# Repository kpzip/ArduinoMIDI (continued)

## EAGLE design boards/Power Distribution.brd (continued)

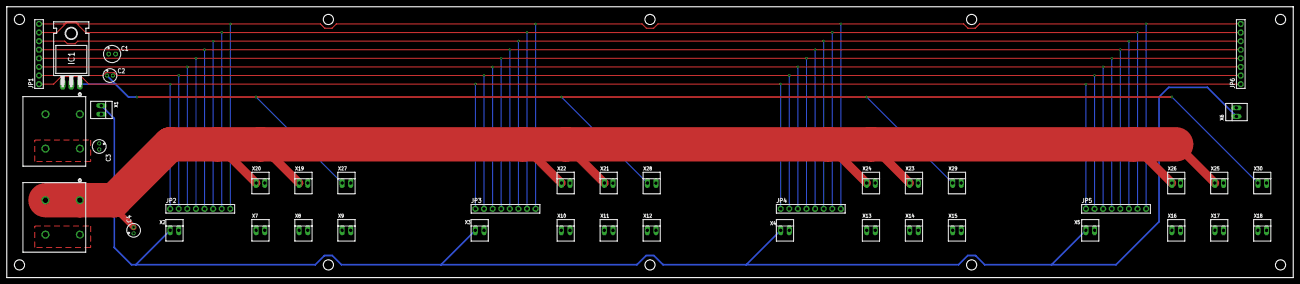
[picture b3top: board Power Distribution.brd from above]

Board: 2 copper layers, 380.0 x 80.0 mm, 43 parts (0 on the bottom side), 13 nets.

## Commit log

2024-03-26 project setup
2024-10-10 add board files
2024-10-10 make eagle files visible as language
